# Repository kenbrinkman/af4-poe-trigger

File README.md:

# aF4 Frozen Feeder — ESP32 PoE Trigger

Replaces the inD connect WiFi dongle on the [inD aquatics aF4](https://www.indaquatics.com/products/af4) refrigerated frozen-food feeder with an Olimex ESP32-POE-ISO running ESPHome, triggering feeds via the aF4's 0-10V port and scheduled from Home Assistant.

## How it works

ESP32-POE-ISO → GPIO32 → 220Ω → AQY212GS PhotoMOS → switches the feeder's own 12V supply (regulated to ~10.4V by an on-board LM1117-ADJ) onto the 3.5mm trigger jack. Safety guardrails (20s pulse, 5-min lockout, restore-off, flash-persisted boot lockout) are baked into the ESPHome config on-device; HA is scheduler only.

**Rev E** puts all of that on a PCB "hat" that plugs onto the ESP32's EXT1/EXT2 headers and carries both panel connectors, assembled by PCBWay. The rev C hand-wired protoboard is retired.

> The trigger pin is **GPIO32**, not GPIO13. The Olimex board has a factory 2.2 kΩ pull-up on GPIO13 that can partially turn the PhotoMOS on during boot. See `docs/aF4-pcb-notes.md`.

## Where to start

| You are | Read |
|---|---|
| **A person, new to this project** | This file, then `STATUS.md` for where it stands, then `aF4-MASTER-REFERENCE.md` §1 and §2 |
| **An AI session** | `.claude/CLAUDE.md`, then `STATUS.md`. **Nothing else by default** — the routing table in `.claude/CLAUDE.md` §7 says where each answer lives |

Three documents are live. `STATUS.md` is the only one that describes current state; it is
rewritten, never appended to. `aF4-MASTER-REFERENCE.md` is the deep record — it carries a
section index and is meant to be grepped by `§N.N`, not read whole. `.claude/CLAUDE.md` holds
the durable facts and the routing table.

## Folder map

| Path | Contents |
|---|---|
| `STATUS.md` | **The only live-status doc.** Phase, what you may trust, open items |
| `aF4-MASTER-REFERENCE.md` | **The record.** Every load-bearing claim tagged with its provenance (measured / datasheet / calculated / asserted). Section-indexed |
| `.claude/CLAUDE.md` | Durable priming for AI sessions + the routing table |
| `.claude/settings.json` | Claude Code project settings and hooks — see `docs/git-rules.md` |
| `tools/` | `tools/section_index.py` — regenerates the master reference's section index |
| `docs/` | Subsystem references: feeder spec, PCB notes, BOM, assembly guide, enclosure notes, vendor-doc notes, meter test battery, and `docs/git-rules.md` |
| `firmware/` | `firmware/af4-feeder.yaml` — the ESPHome config as flashed, **source of truth**. `firmware/secrets.yaml` is gitignored |
| `hardware/enclosure/` | `hardware/enclosure/af4_enclosure_ocp.py` (parametric source, self-checking) and its STEP/STL exports; the printable rev E hat stand-in |
| `pcb/` | KiCad project, `pcb/gen_pcb.py` generator, the PCBWay upload package and the order record |
| `reference/diagrams/` | Wiring and system SVGs |
| `reference/vendor/` | Vendor CAD and PDFs — gitignored, not redistributed |
| `archive/` | 🚫 **Not authoritative and not in the read path.** Superseded handoff, the three dated reviews, rev C protoboard history. See `archive/README.md` |

## The board

`pcb/gen_pcb.py` is the source of truth: it generates `pcb/af4-trigger-hat.kicad_pcb`
deterministically from named coordinates, taken directly from the Olimex Rev N
KiCad source so the sockets line up by construction. Edit the script, not the
board file, then re-run it and `pcb/post.py` (fills the copper pours and runs DRC).

`pcb/af4-trigger-hat-rev-E-PCBWay.zip` is what you upload: Gerbers, drill, BOM,
centroid, fab notes.

## Vendor files (not in repo)

- ESP32-POE-ISO board CAD: [Olimex hardware files](https://github.com/OLIMEX/ESP32-POE-ISO)
- AQY212 PhotoMOS STEP: Panasonic
- aF4 / inD connect product docs: [inD aquatics](https://www.indaquatics.com/products/af4)

## Key trigger rules (inD 0-10V spec)

Feed triggers on ≥9V held ≥15s (inD publishes 6s/10s/15s across three guides — design to the longest); feeds ≥5 min apart; port must see ~0V for >60s to re-arm. Connecting the link port **overrides the aF4's internal 24h schedule** — an offline ESP32 means no feeding at all. Measured OEM dongle trigger voltage 10.37V open-circuit (don't feed raw 12V).

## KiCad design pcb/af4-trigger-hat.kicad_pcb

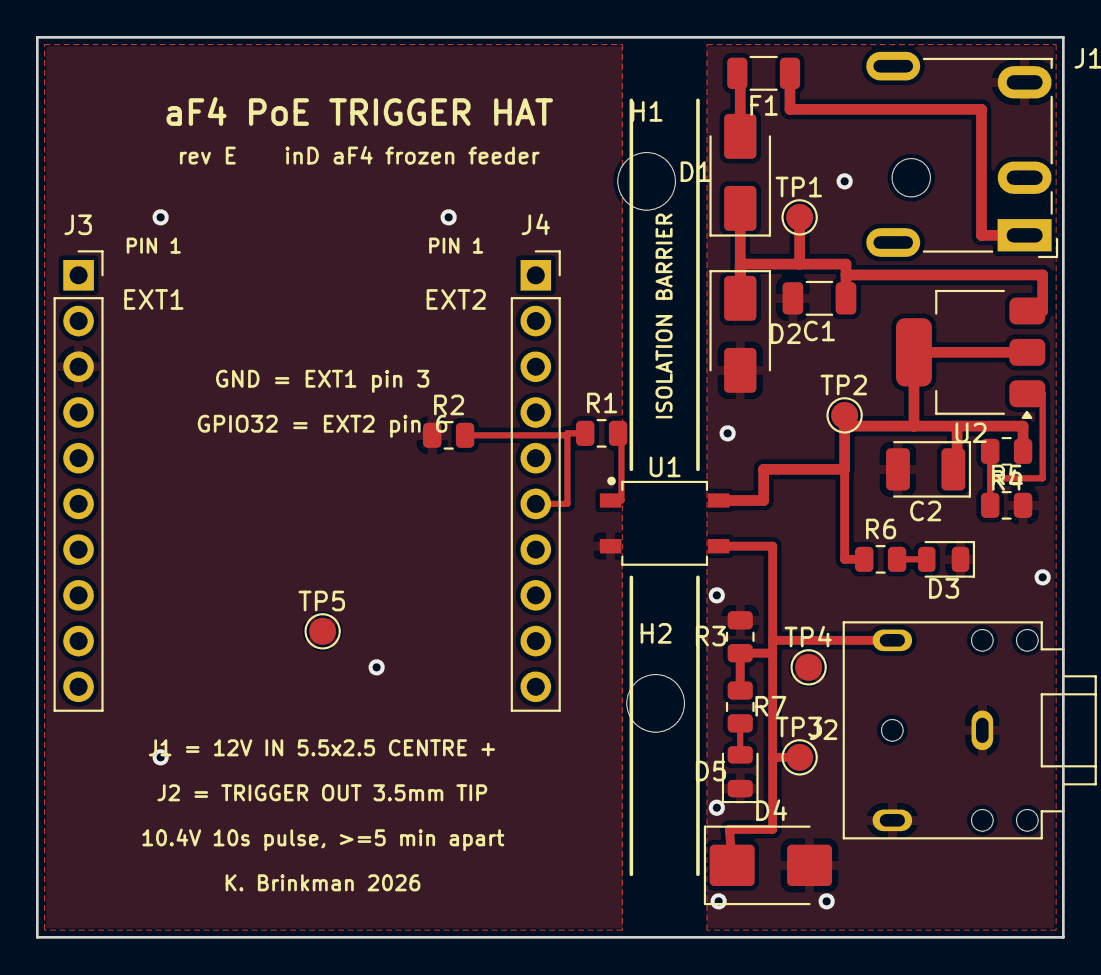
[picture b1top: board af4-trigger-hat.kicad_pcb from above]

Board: 2 copper layers, 57.0 x 50.0 mm, 28 parts (0 on the bottom side), 12 nets.

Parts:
C1: 10uF/50V; C_1206_3216Metric
C2: 10uF/25V; CP_EIA-3528-21_Kemet-B
D1: SS14; D_SMA
D2: SMAJ13A; D_SMA
D3: GRN; LED_0805_2012Metric
D4: SMBJ13CA; D_SMB
D5: YEL; LED_0805_2012Metric
F1: 010; R_1206_3216Metric
H1, H2: M3; MountingHole_3.2mm_M3_ISO7380
J1: PJ-079BH; BarrelJack_CUI_PJ-079BH_Horizontal
J2: SJ1-3523N; Jack_3.5mm_CUI_SJ1-3523N_Horizontal
J3: EXT1; PinSocket_1x10_P2.54mm_Vertical
J4: EXT2; PinSocket_1x10_P2.54mm_Vertical
R1: 220R; R_0805_2012Metric
R2: 10k; R_0805_2012Metric
R3: 100k; R_0805_2012Metric
R4: 121R; R_0805_2012Metric
R5: 887R; R_0805_2012Metric
R6: 1k0; R_0805_2012Metric
R7: 6k8; R_0805_2012Metric
TP1: 12V; TestPoint_Pad_D1.5mm
TP2: 10V4; TestPoint_Pad_D1.5mm
TP3: TIP; TestPoint_Pad_D1.5mm
TP4: GND; TestPoint_Pad_D1.5mm
TP5: GNDL; TestPoint_Pad_D1.5mm
U1: AQY212GS; AQY212GS_SOP4_Panasonic
U2: LM1117MPX-ADJ; SOT-223-3_TabPin2

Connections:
+10V4: C2.1, R4.1, R6.1, TP2.1, U1.4, U2.2
+12V: C1.1, D1.1, D2.1, TP1.1, U2.3
+12V_F: D1.2, F1.2
+12V_RAW: F1.1, J1.1
ADJ: R4.2, R5.1, U2.1
FEEDLED: D5.2, R7.2
GNDL: J3.3, R2.1, TP5.1, U1.2
GNDP: C1.2, C2.2, D2.2, D3.1, D4.2, D5.1, J1.2, J2.R, J2.S, R3.2, R5.2, TP4.1
GPIO32: J4.6, R1.1, R2.2
LED_A: R1.2, U1.1
PWRLED: D3.2, R6.2
TIP: D4.1, J2.T, R3.1, R7.1, TP3.1, U1.3

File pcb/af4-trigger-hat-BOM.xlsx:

Line# | Quantity Per Part Number | Reference Designator | Part Number | Part Description | Package | Type | Manufacturers Name | Manufacturers Part Number | Distributors Part Number | Notes
1 | 1 | U1 | AQY212GS | PhotoMOS solid-state relay, 1 Form A, 60 V / 1 A, 1500 Vrms isolation | SOP-4 | SMD | Panasonic | AQY212GS |  | Isolates ESP32 logic from the feeder supply. Pins 3/4 are a symmetric MOSFET pa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
2 | 1 | U2 | LM1117MPX-ADJ/NOPB | LDO regulator, adjustable, 800 mA | SOT-223 | SMD | Texas Instruments | LM1117MPX-ADJ/NOPB |  | Tab is VOUT. Set to 10.4 V by R4/R5.
3 | 1 | D1 | SS14-E3/61T | Schottky rectifier, 40 V / 1 A | SMA (DO-214AC) | SMD | Vishay | SS14-E3/61T |  | Reverse-polarity protection, in series with the 12 V input.
4 | 1 | D2 | SMAJ13A | TVS diode, unidirectional, 13 V standoff, 400 W | SMA (DO-214AC) | SMD | Littelfuse | SMAJ13A |  | Input clamp. Standoff sits above the 12 V rail; cathode to +12 V.
5 | 1 | D4 | SMBJ13CA | TVS diode, bidirectional, 13 V standoff, 600 W | SMB (DO-214AA) | SMD | Littelfuse | SMBJ13CA |  | Across the trigger pair at the jack. Bidirectional - no orientation.
6 | 1 | D3 | APT2012SGC | LED, green, 2.2 V typ | 0805 | SMD | Kingbright | APT2012SGC |  | 10.4 V rail live indicator.
7 | 1 | D5 | APT2012SYCK | LED, yellow, 2.0 V typ | 0805 | SMD | Kingbright | APT2012SYCK |  | Lights while the trigger output is asserted.
8 | 1 | F1 | 1206L010/60WR | PPTC resettable fuse, 0.10 A hold / 0.25 A trip, 60 V | 1206 | SMD | Littelfuse | 1206L010/60WR |  | On the 12 V tap. Feeder supply can source 12.5 A.
9 | 1 | C1 | GRM31CR61H106KA12L | Capacitor, 10 uF, 50 V, X5R | 1206 | SMD | Murata | GRM31CR61H106KA12L |  | Regulator input bulk.
10 | 1 | C2 | T491B106K025AT | Capacitor, tantalum, 10 uF, 25 V | EIA-3528 (case B) | SMD | Kemet | T491B106K025AT |  | Regulator output. Tantalum is required - the LM1117 needs output-cap ESR. POLAR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
11 | 1 | R1 | RC0805FR-07220RL | Resistor, 220 R, 1%, 1/8 W | 0805 | SMD | Yageo | RC0805FR-07220RL |  | PhotoMOS LED current set, ~9 mA from GPIO32.
12 | 1 | R2 | RC0805FR-0710KL | Resistor, 10 k, 1%, 1/8 W | 0805 | SMD | Yageo | RC0805FR-0710KL |  | GPIO32 pulldown - holds the PhotoMOS off at boot.
13 | 1 | R3 | RC0805FR-07100KL | Resistor, 100 k, 1%, 1/8 W | 0805 | SMD | Yageo | RC0805FR-07100KL |  | Trigger-line bleed, guarantees the 0 V re-arm.
14 | 1 | R4 | RC0805FR-07121RL | Resistor, 121 R, 1%, 1/8 W | 0805 | SMD | Yageo | RC0805FR-07121RL |  | LM1117 divider, VOUT to ADJ.
15 | 1 | R5 | RC0805FR-07887RL | Resistor, 887 R, 1%, 1/8 W | 0805 | SMD | Yageo | RC0805FR-07887RL |  | LM1117 divider, ADJ to GND. Vout = 1.25*(1+887/121) + Iadj*887 = 10.47 V.
16 | 1 | R6 | RC0805FR-071KL | Resistor, 1.0 k, 1%, 1/8 W | 0805 | SMD | Yageo | RC0805FR-071KL |  | D3 green LED series resistor. 8.2 mA - APT2012SGC is only 12 mcd at 20 mA, so i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
17 | 1 | R7 | RC0805FR-076K8L | Resistor, 6.8 k, 1%, 1/8 W | 0805 | SMD | Yageo | RC0805FR-076K8L |  | D5 yellow LED series resistor. 1.2 mA - APT2012SYCK is 150 mcd at 20 mA, so it 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
18 | 1 | J1 | PJ-079BH | DC power jack, 5.5 x 2.5 mm, 2.5 mm centre pin, 24 V / 5 A | Right-angle THT | THT | Same Sky (CUI) | PJ-079BH |  | MUST be the 2.5 mm centre-pin part. Terminal 3 (switch) is unconnected.
19 | 1 | J2 | SJ1-3523N | Audio jack, 3.5 mm, 3-conductor, right angle | THT | THT | Same Sky (CUI) | SJ1-3523N |  | Tip = trigger signal. Ring is tied to sleeve on the board.
20 | 2 | J3,J4 | PPTC101LFBN-RC | Socket header, 1x10, 2.54 mm, vertical | THT | THT | Sullins | PPTC101LFBN-RC |  | Mates the Olimex ESP32-POE-ISO EXT1/EXT2 headers.
